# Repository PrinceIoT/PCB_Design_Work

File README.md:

Repository contain pcb design work done in both Kicard and Altium tools

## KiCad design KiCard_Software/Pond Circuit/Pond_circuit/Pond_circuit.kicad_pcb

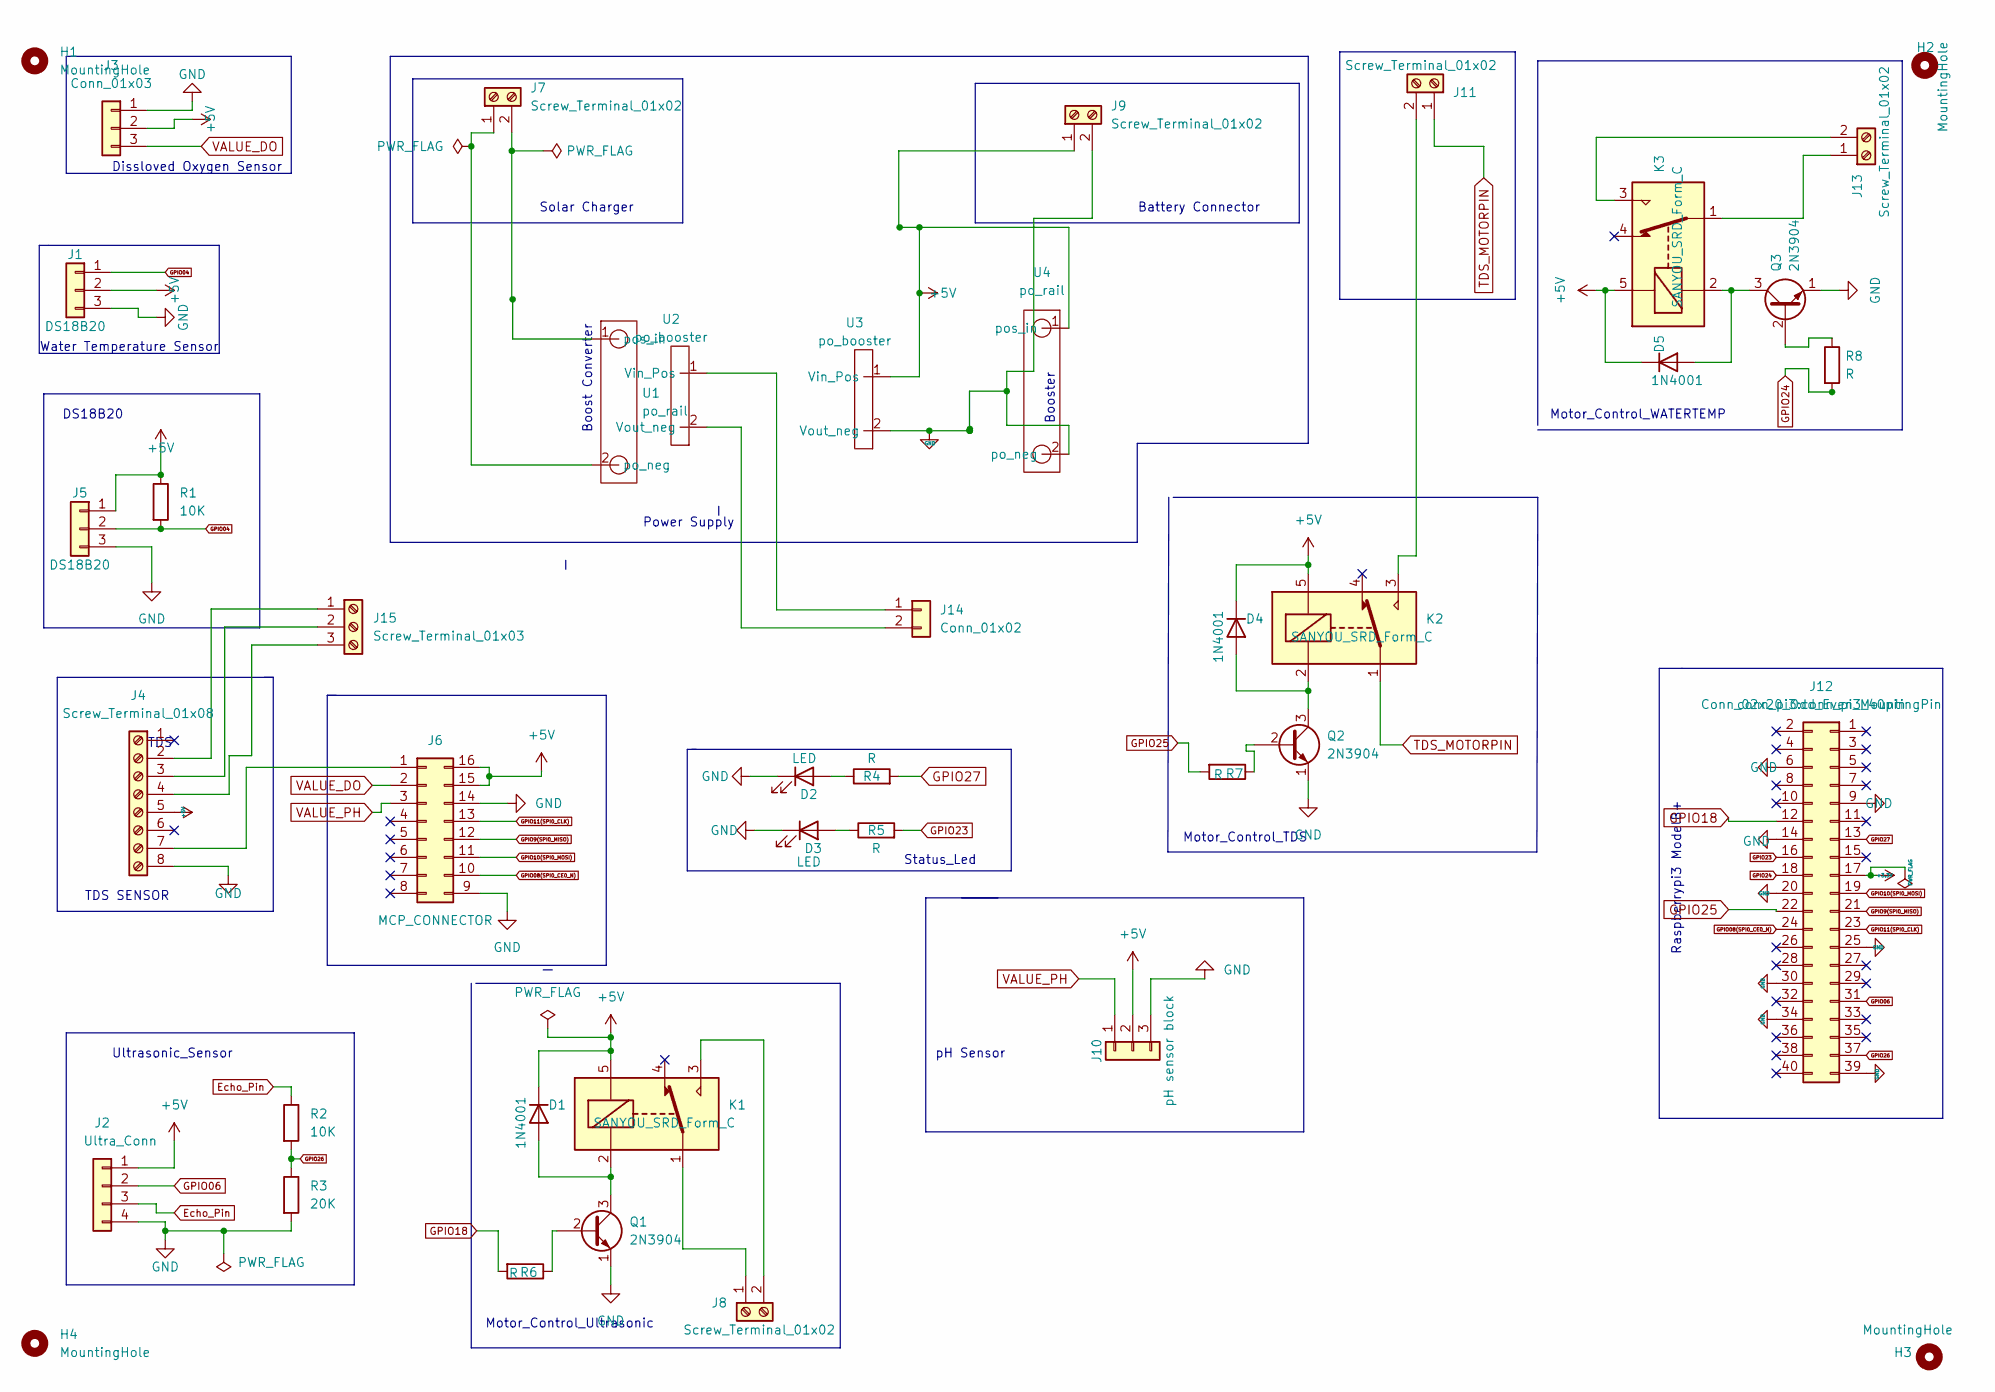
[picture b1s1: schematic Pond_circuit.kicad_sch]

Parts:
D1, D4, D5: 1N4001; D_DO-41_SOD81_P10.16mm_Horizontal
D2, D3: LED; LED_D3.0mm
H1, H2, H3, H4: MountingHole; MountingHole_2.5mm
J1: DS18B20; PinSocket_1x03_P1.00mm_Vertical
J2: Ultra_Conn; PinSocket_1x04_P1.00mm_Vertical
J3: Conn_01x03; PinSocket_1x03_P1.00mm_Vertical
J4: Screw_Terminal_01x08; TDS_FOOT
J5: DS18B20; con3_pin
J6: MCP_CONNECTOR; mcp3008_16
J7, J8, J9, J11, J13: Screw_Terminal_01x02; con2_pin
J10: pH sensor block; con3_pin
J12: Conn_02x20_Odd_Even_MountingPin; conn_pi3_40pin
J14: Conn_01x02; con2_pin
J15: Screw_Terminal_01x03; con3_pin
K1, K2, K3: SANYOU_SRD_Form_C; Relay_SPDT_SANYOU_SRD_Series_Form_C
Q1, Q2, Q3: 2N3904; TO-92_Inline
R1, R2: 10K; R_Axial_DIN0309_L9.0mm_D3.2mm_P12.70mm_Horizontal
R3: 20K; R_Axial_DIN0309_L9.0mm_D3.2mm_P12.70mm_Horizontal
R4, R5: R; R_Axial_DIN0309_L9.0mm_D3.2mm_P15.24mm_Horizontal
R6, R7, R8: R; R_Axial_DIN0411_L9.9mm_D3.6mm_P12.70mm_Horizontal
U1, U4: po_rail; buck_rail
U2, U3: po_booster; boost_rail

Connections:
+3V3: J12.17
+5V: D1.1 (K), D4.1 (K), D5.1 (K), J1.2, J2.1, J3.2, J4.5, J5.1, J6.15 (Pin_2b), J6.16 (Pin_1b), J9.1, J10.2, K1.5, K2.5, K3.5, R1.1, U3.1 (Vin_Pos), U4.1 (pos_in)
Echo_Pin: J2.3, R2.1
GND: D2.1 (K), D3.1 (K), J1.3, J2.4, J3.1, J4.8, J5.3, J6.9 (Pin_8b), J6.14 (Pin_3b), J9.2, J10.3, J12.6, J12.9, J12.14, J12.20, J12.25, J12.30, J12.34, J12.39, Q1.1 (E), Q2.1 (E), Q3.1 (E), R3.2, U3.2 (Vout_neg), U4.2 (po_neg)
GPIO04: J1.1, J5.2, R1.2
GPIO06: J2.2, J12.31
GPIO08(SPI0_CE0_N): J6.10 (Pin_7b), J12.24
GPIO9(SPI0_MISO): J6.12 (Pin_5b), J12.21
GPIO10(SPI0_MOSI): J6.11 (Pin_6b), J12.19
GPIO11(SPI0_CLK): J6.13 (Pin_4b), J12.23
GPIO18: J12.12, R6.2
GPIO23: J12.16, R5.2
GPIO24: J12.18, R8.2
GPIO25: J12.22, R7.2
GPIO26: J12.37, R2.2, R3.1
GPIO27: J12.13, R4.2
unnamed: D1.2 (A), K1.2, Q1.3 (C)
unnamed: D2.2 (A), R4.1
unnamed: D3.2 (A), R5.1
unnamed: D4.2 (A), K2.2, Q2.3 (C)
unnamed: D5.2 (A), K3.2, Q3.3 (C)
unnamed: J4.7, J6.1 (Pin_1a)
unnamed: J7.1, U1.2 (po_neg)
unnamed: J7.2, U1.1 (pos_in)
unnamed: J8.1, K1.1
unnamed: J8.2, K1.3
unnamed: J11.2, K2.3
unnamed: J13.1, K3.1
unnamed: J13.2, K3.3
unnamed: J14.1, U2.1 (Vin_Pos)
unnamed: J14.2, U2.2 (Vout_neg)
unnamed: J4.2, J15.1
unnamed: J4.3, J15.2
unnamed: J4.4, J15.3
unnamed: Q1.2 (B), R6.1
unnamed: Q2.2 (B), R7.1
unnamed: Q3.2 (B), R8.1
TDS_MOTORPIN: J11.1, K2.1
VALUE_DO: J3.3, J6.2 (Pin_2a)
VALUE_PH: J6.3 (Pin_3a), J10.1

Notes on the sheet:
Boost Converter
Dissloved Oxygen Sensor
TDS
Raspberrypi3 ModelB+
pH Sensor
TDS SENSOR
Status_Led
Water Temperature Sensor
Battery Connector
Power Supply
Motor_Control_TDS
Ultrasonic_Sensor
Motor_Control_Ultrasonic
Solar Charger
DS18B20
Booster
Motor_Control_WATERTEMP

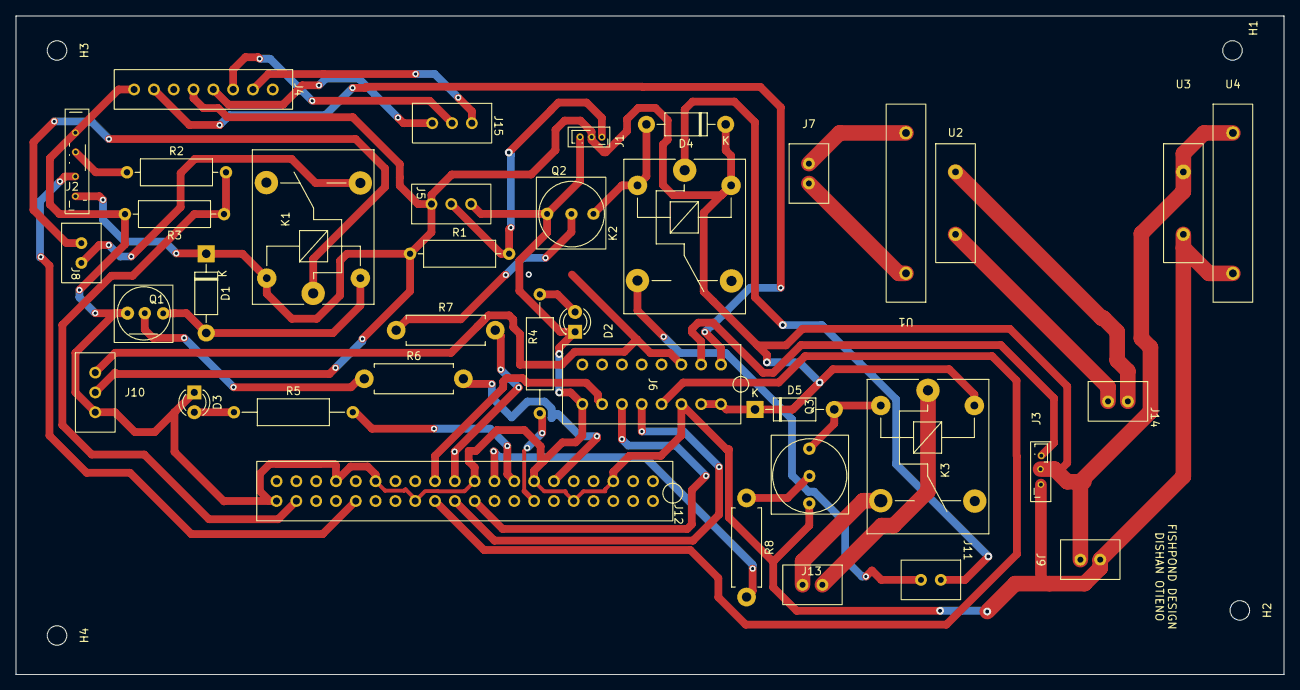
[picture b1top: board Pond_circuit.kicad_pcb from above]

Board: 2 copper layers, 162.6 x 84.4 mm, 42 parts (0 on the bottom side), 39 nets.

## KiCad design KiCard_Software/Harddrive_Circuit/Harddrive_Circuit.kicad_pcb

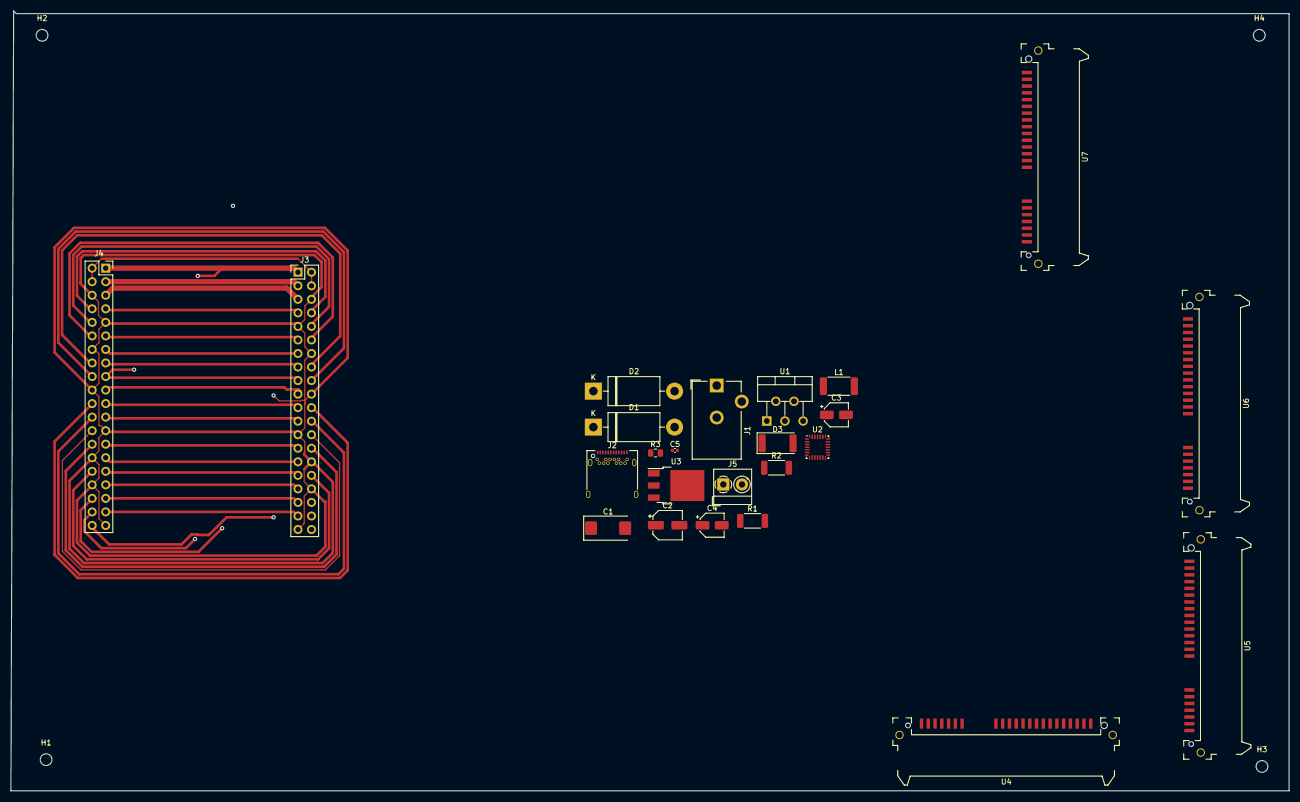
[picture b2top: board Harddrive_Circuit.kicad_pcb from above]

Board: 2 copper layers, 239.8 x 146.3 mm, 28 parts (0 on the bottom side), 42 nets.

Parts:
C1: 680uF; CP_EIA-7343-43_Kemet-X_Pad2.25x2.55mm_HandSolder
C2: 220uF; CP_Elec_5x5.8
C3: 10uF/50V; CP_Elec_4x3
C4: 22uF/50V; CP_Elec_4x4.5
C5: 0.1uF; C_0402_1005Metric
D1: 1N5400; D_DO-201AD_P15.24mm_Horizontal
D2: 1N5822; D_DO-201AD_P15.24mm_Horizontal
D3: LED; LED_2512_6332Metric
H1, H2, H3, H4: MountingHole; MountingHole_2.2mm_M2
J1: Barrel_Jack_Switch; BarrelJack_CUI_PJ-102AH_Horizontal
J2: USB_C_Receptacle; USB_C_Receptacle_Amphenol_12401548E4-2A
J3: Connector_Generic_Conn_02x20_Odd_Even; PinHeader_2x20_P2.54mm_Vertical
J4: Connector_Generic_Conn_02x20_Odd_Even; PinSocket_2x20_P2.54mm_Vertical
J5: Screw_Terminal_01x02; TerminalBlock_MetzConnect_Type059_RT06302HBWC_1x02_P3.50mm_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
L1: 33uH; L_2512_6332Metric
R1, R2: 5.1K; R_2010_5025Metric
R3: 220ohms; R_0805_2012Metric
U1: LM2596T-5; TO-220-5_P3.4x3.7mm_StaggerOdd_Lead3.8mm_Vertical
U2: MAX14661ETI_; QFN-28_4x4mm_P0.5mm
U3: LM1117-3.3; TO-252-3_TabPin2
U4, U5, U6, U7: sata; SATA_Amphenol_10029364-001LF_Horizontal

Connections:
5V: J3.2, J3.4, J4.2, J4.4
+3.3V: J3.1, J3.17, J4.1, J4.17
+3V3: C4.1, C5.1, U2.1 (SPI/~I2C), U2.22 (~SD), U2.26 (VCC), U3.2 (VO)
+5V: C2.1, C3.1, J2.A4 (VBUS), J2.A9 (VBUS), J2.B4 (VBUS), J2.B9 (VBUS), J5.2, L1.2, R3.1, U1.4 (FB), U3.3 (VI)
+12V: D1.1 (K), U1.1 (VIN)
GND: C1.2, C2.2, C3.2, C4.2, C5.2, D2.2 (A), D3.1 (K), J1.2, J1.3, J2.A1 (GND), J2.A12 (GND), J2.B1 (GND), J2.B12 (GND), J2.S1 (SHIELD), J3.6, J3.9, J3.14, J3.20, J3.25, J3.30, J3.34, J3.39, J4.6, J4.9, J4.14, J4.20, J4.25, J4.30, J4.34, J4.39, J5.1, R1.2, R2.2, U1.3 (GND), U2.11 (GND), U2.25 (GND), U3.1 (GND)
GPIO2_SDA1: J4.3, U2.27 (DIN/SDA)
GPIO3_SCL1: J3.5, J4.5
GPIO4_GPIO_GCLK: J3.7, J4.7
GPIO5: J3.29, J4.29
GPIO6: J3.31, J4.31
GPIO7_SPI_CE1_N: J3.26, J4.26
GPIO8_SPI_CE0_N: J4.24, U2.23 (CS/A0)
GPIO9_SPI_MISO: J3.21, J4.21
GPIO10_SPI_MOSI: J3.19, J4.19
GPIO11_SPI_SCLK: J4.23, U2.24 (SCLK/SCL)
GPIO12: J3.32, J4.32
GPIO13: J3.33, J4.33
GPIO14_TXD0: J3.8, J4.8
GPIO15_RXD0: J3.10, J4.10
GPIO16: J3.36, J4.36
GPIO17_GEN0: J3.11, J4.11
GPIO18_GEN1: J3.12, J4.12
GPIO19: J3.35, J4.35
GPIO20: J3.38, J4.38
GPIO21: J3.40, J4.40
GPIO22_GEN3: J3.15, J4.15
GPIO23_GEN4: J3.16, J4.16
GPIO24_GEN5: J3.18, J4.18
GPIO25_GEN6: J3.22, J4.22
GPIO26: J3.37, J4.37
GPIO27_GEN2: J3.13, J4.13
ID_SC: J3.28, J4.28
ID_SD: J3.27, J4.27
unnamed: C1.1, U1.5 (~ON/OFF)
unnamed: D1.2 (A), J1.1
unnamed: D2.1 (K), L1.1, U1.2 (OUT)
unnamed: D3.2 (A), R3.2
unnamed: J2.A5 (CC1), R1.1
unnamed: J2.A6 (D+), J2.B6 (D+), U2.13 (COMB)
unnamed: J2.A7 (D-), J2.B7 (D-), U2.10 (COMA)
unnamed: J2.B5 (CC2), R2.1

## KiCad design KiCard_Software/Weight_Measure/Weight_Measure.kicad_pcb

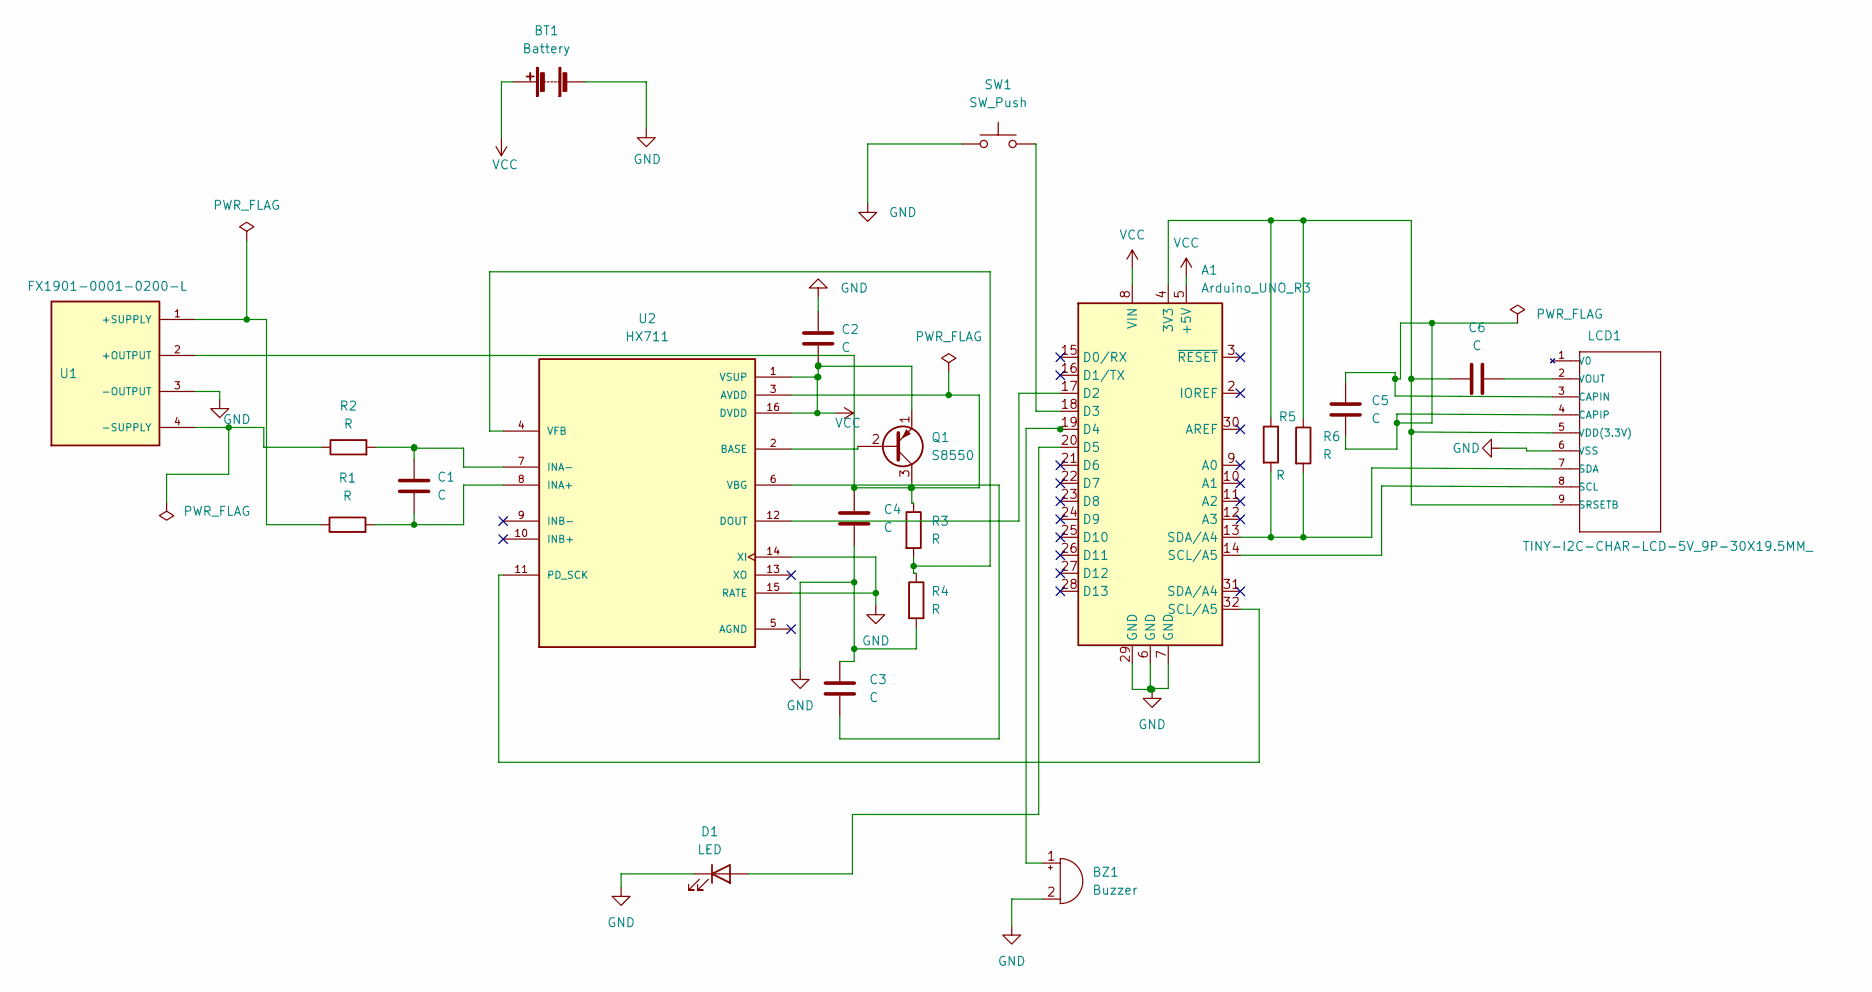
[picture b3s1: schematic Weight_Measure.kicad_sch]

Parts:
A1: Arduino_UNO_R3; Arduino_UNO_R3_WithMountingHoles
BT1: Battery; BatteryHolder_Bulgin_BX0036_1xC
BZ1: Buzzer; Buzzer_D14mm_H7mm_P10mm
C1, C2, C3, C4, C5, C6: C; C_Axial_L3.8mm_D2.6mm_P12.50mm_Horizontal
D1: LED; LED_D3.0mm
LCD1: TINY-I2C-CHAR-LCD-5V_9P-30X19.5MM_; LCD9-1.5-30X19.5MM; MPN 12 LCD Breadout
Q1: S8550; TO-92_Inline
R1, R2, R3, R4, R5, R6: R; R_Axial_DIN0309_L9.0mm_D3.2mm_P15.24mm_Horizontal
SW1: SW_Push; SW_PUSH_6mm
U1: FX1901-0001-0200-L; SENSOR_FX1901-0001-0200-L
U2: HX711; SOP127P600X180-16N; PARTREV V2.0

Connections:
GND: A1.6 (GND), A1.7 (GND), A1.29 (GND), BT1.2 (-), BZ1.2 (+), C2.1, C3.1, C4.2, D1.1 (K), LCD1.6 (VSS), R4.2, SW1.1, U1.3 (-OUTPUT), U2.14 (XI), U2.15 (RATE)
unnamed: A1.4 (3V3), C6.1, LCD1.5 (VDD(3.3V)), LCD1.9 (SRSETB), R5.1, R6.1
unnamed: A1.13 (SDA/A4), LCD1.7 (SDA), R5.2, R6.2
unnamed: A1.14 (SCL/A5), LCD1.8 (SCL)
unnamed: A1.17 (D2), U2.12 (DOUT)
unnamed: A1.18 (D3), SW1.2
unnamed: A1.19 (D4), BZ1.1 (-)
unnamed: A1.20 (D5), D1.2 (A)
unnamed: A1.32 (SCL/A5), U2.11 (PD_SCK)
unnamed: C1.1, R2.2, U2.7 (INA-)
unnamed: C1.2, R1.2, U2.8 (INA+)
unnamed: C3.2, U2.6 (VBG)
unnamed: C4.1, U1.2 (+OUTPUT)
unnamed: C5.1, C5.2, LCD1.3 (CAPIN), LCD1.4 (CAPIP)
unnamed: C6.2, LCD1.2 (VOUT)
unnamed: Q1.2 (B), U2.2 (BASE)
unnamed: Q1.3 (C), R3.1, U2.3 (AVDD)
unnamed: R1.1, U1.1 (+SUPPLY)
unnamed: R2.1, U1.4 (-SUPPLY)
unnamed: R3.2, R4.1, U2.4 (VFB)
VCC: A1.5 (+5V), A1.8 (VIN), BT1.1 (+), C2.2, Q1.1 (E), U2.1 (VSUP), U2.16 (DVDD)

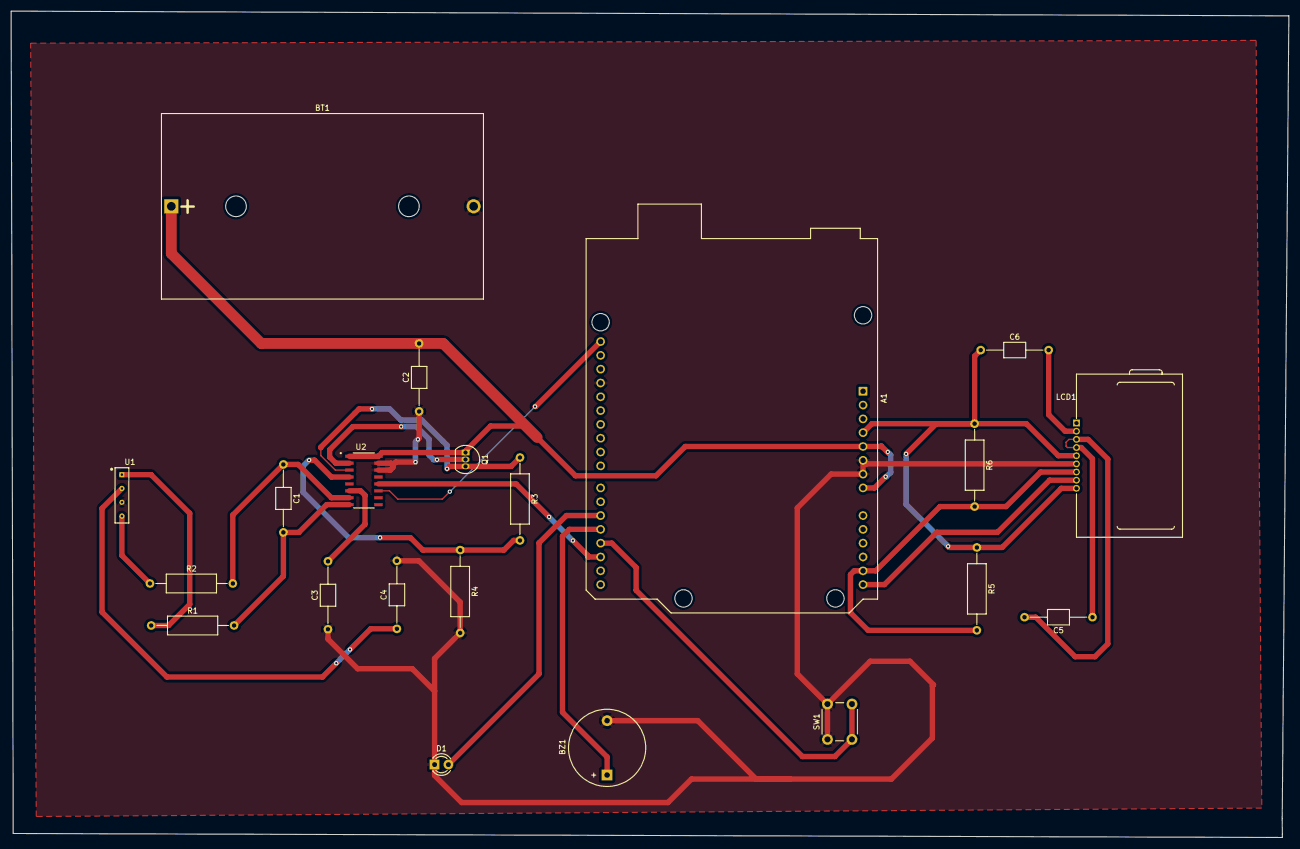
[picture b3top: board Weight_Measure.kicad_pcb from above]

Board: 2 copper layers, 235.0 x 152.0 mm, 21 parts (0 on the bottom side), 21 nets.

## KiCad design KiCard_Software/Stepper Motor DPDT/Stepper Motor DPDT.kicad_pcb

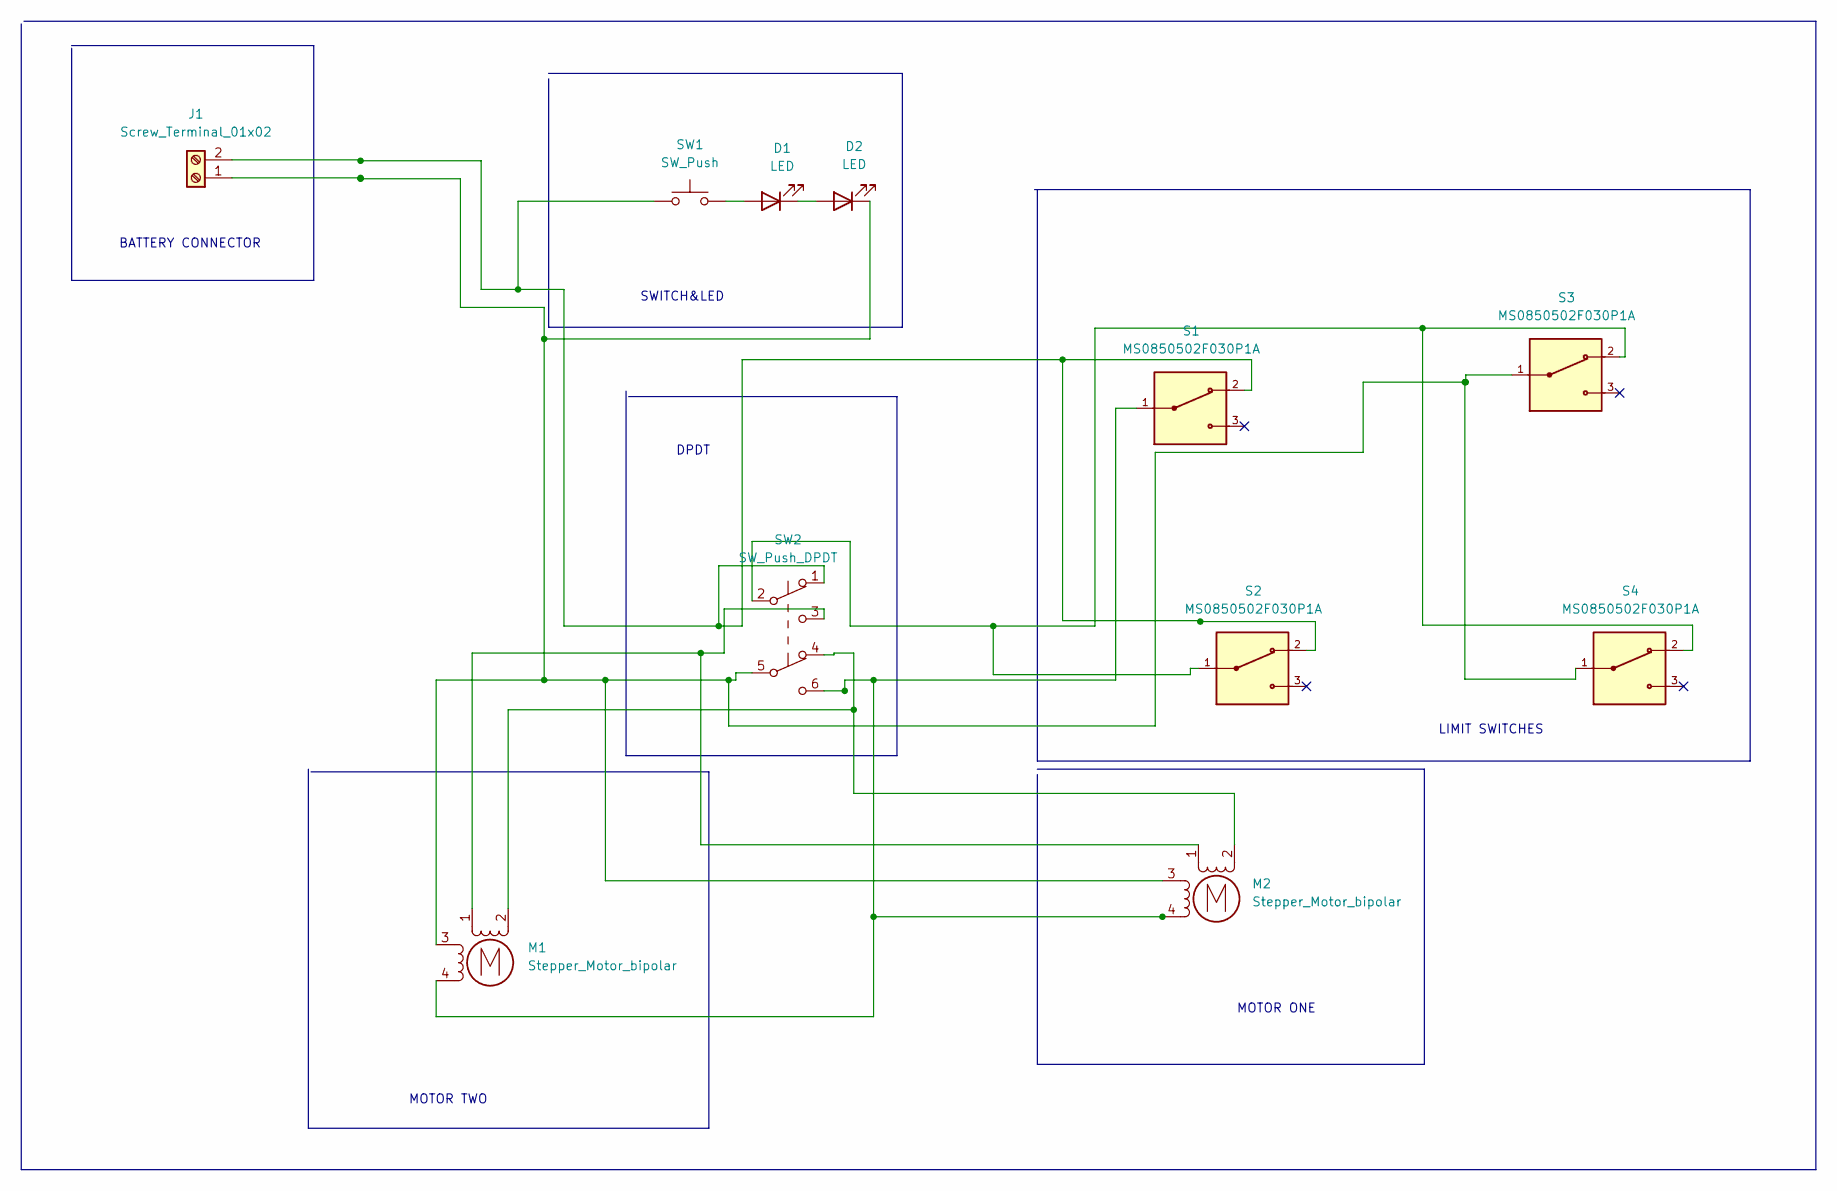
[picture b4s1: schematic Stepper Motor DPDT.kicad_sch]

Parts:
D1, D2: LED; LED_D3.0mm_Clear
J1: Screw_Terminal_01x02; TerminalBlock_Phoenix_MKDS-3-2-5.08_1x02_P5.08mm_Horizontal
M1, M2: Stepper_Motor_bipolar; TerminalBlock_MetzConnect_Type059_RT06304HBWC_1x04_P3.50mm_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
S1, S2, S3, S4: MS0850502F030P1A; SW_MS0850502F030P1A
SW1: SW_Push; SW_PUSH_6mm
SW2: SW_Push_DPDT; SW_E-Switch_EG2219_DPDT_Angled

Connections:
unnamed: D1.1 (K), D2.2 (A)
unnamed: D1.2 (A), SW1.2
unnamed: D2.1 (K), J1.1, M1.3, M2.3, S3.1, S4.1, SW2.5 (B)
unnamed: J1.2, S1.2, S2.2, SW1.1, SW2.1 (A)
unnamed: M1.1, M2.1, SW2.3 (C)
unnamed: M1.2 (-), M2.2 (-), SW2.4 (A)
unnamed: M1.4, M2.4, S1.1, SW2.6 (C)
unnamed: S2.1, S3.2, S4.2, SW2.2 (B)

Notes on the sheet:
DPDT
SWITCH&LED
MOTOR TWO
MOTOR ONE
LIMIT SWITCHES
BATTERY CONNECTOR

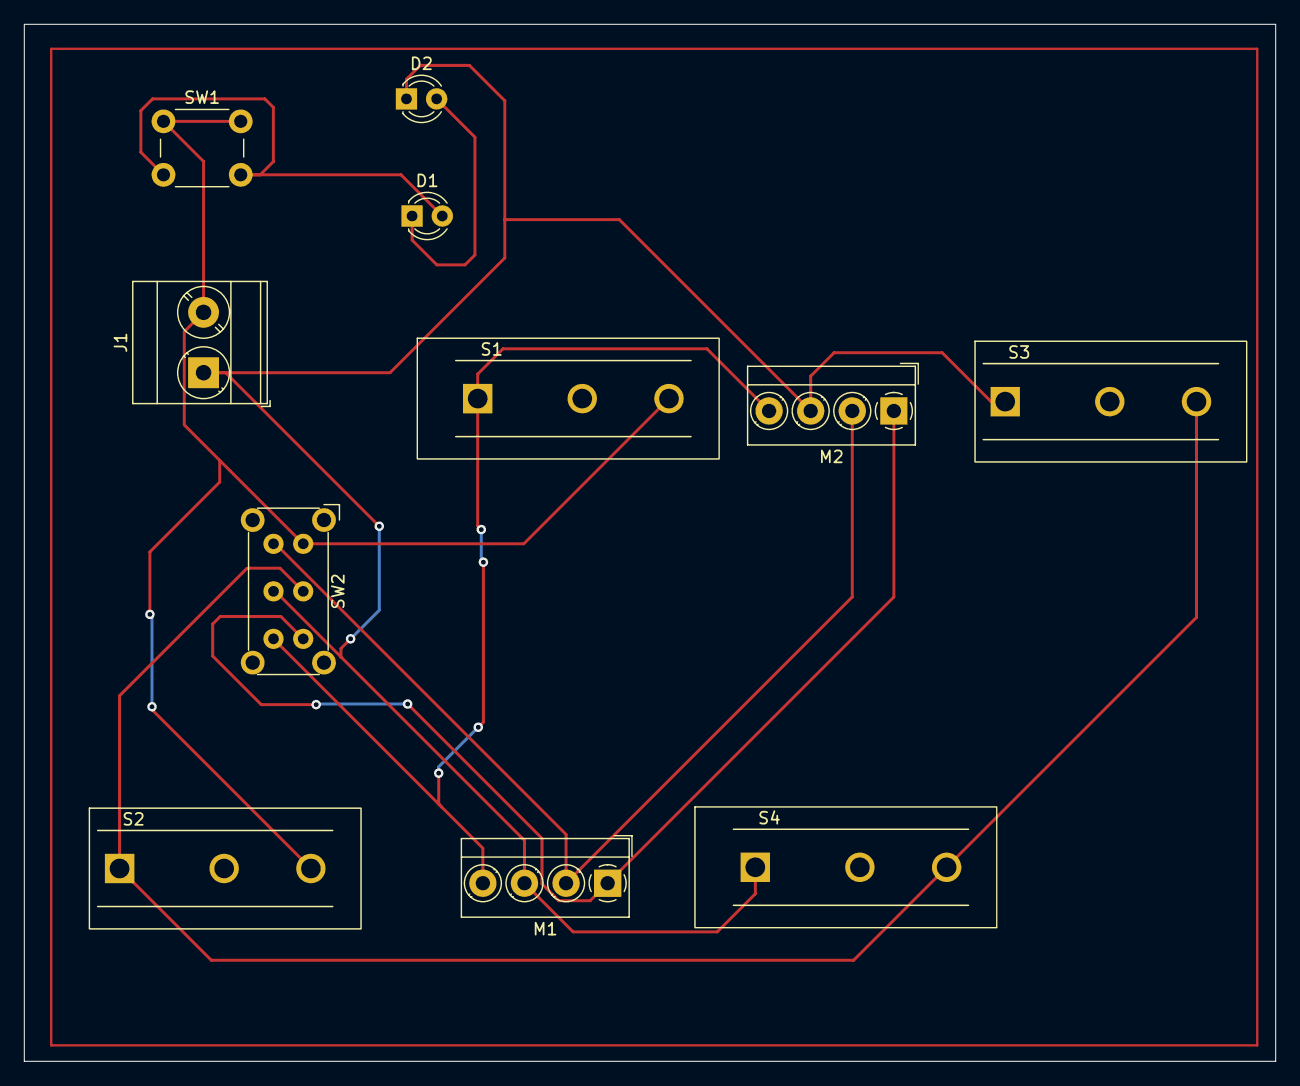
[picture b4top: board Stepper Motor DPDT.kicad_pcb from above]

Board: 2 copper layers, 105.3 x 87.3 mm, 11 parts (0 on the bottom side), 8 nets.

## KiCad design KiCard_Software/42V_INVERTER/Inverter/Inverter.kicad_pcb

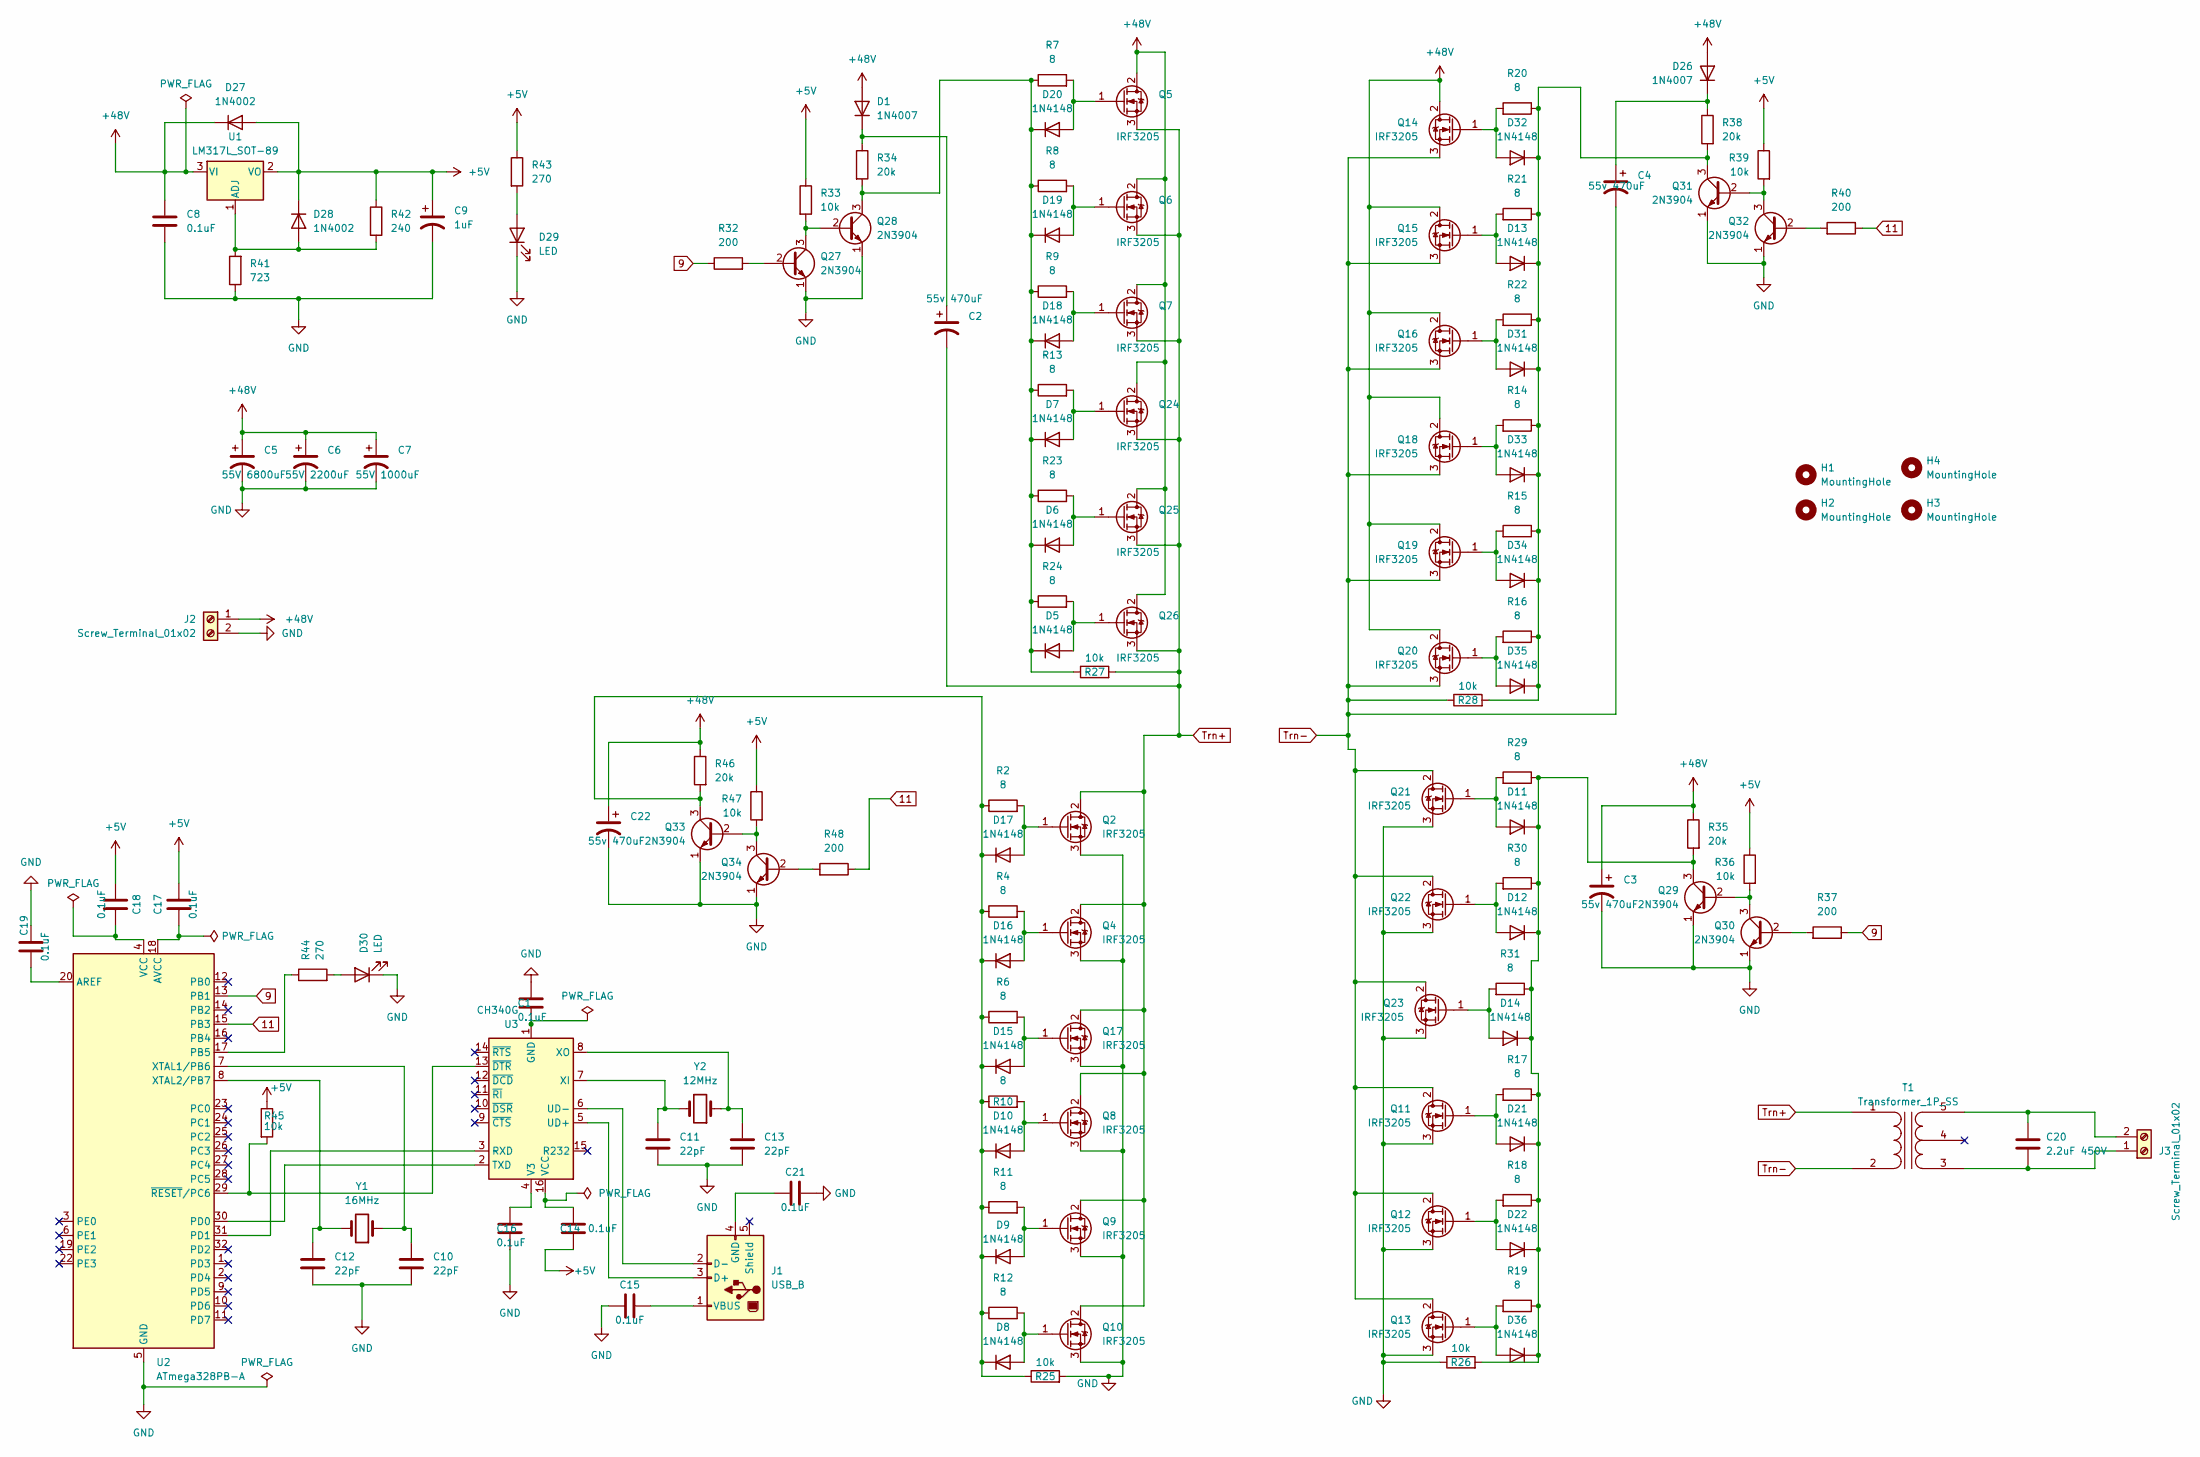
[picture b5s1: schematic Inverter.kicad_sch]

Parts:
C1, C8, C14, C15, C16, C17, C18, C19, C21: 0.1uF; C_Radial_D6.3mm_H7.0mm_P2.50mm
C2, C3, C4, C22: 55v 470uF; CP_Radial_D6.3mm_P2.50mm
C5: 55V 6800uF; CP_Elec_6.3x5.9
C6: 55V 2200uF; CP_Elec_6.3x5.9
C7: 55V 1000uF; CP_Elec_6.3x5.7
C9: 1uF; CP_Radial_D6.3mm_P2.50mm
C10, C11, C12, C13: 22pF; C_Disc_D3.8mm_W2.6mm_P2.50mm
C20: 2.2uF 450V; C_Rect_L18.0mm_W5.0mm_P15.00mm_FKS3_FKP3
D1, D26: 1N4007; D_DO-41_SOD81_P10.16mm_Horizontal
D5, D6, D7, D8, D9, D10, D11, D12, D13, D14, D15, D16, D17, D18, D19, D20, D21, D22, D31, D32, D33, D34, D35, D36: 1N4148; D_DO-35_SOD27_P7.62mm_Horizontal
D27, D28: 1N4002; D_DO-41_SOD81_P10.16mm_Horizontal
D29: LED; LED_1206_3216Metric
D30: LED; LED_2010_5025Metric
H1, H2, H3, H4: MountingHole; MountingHole_2.2mm_M2
J1: USB_B; USB_A_CNCTech_1001-011-01101_Horizontal
J2, J3: Screw_Terminal_01x02; TerminalBlock_Phoenix_MKDS-3-2-5.08_1x02_P5.08mm_Horizontal
Q2, Q4, Q5, Q6, Q7, Q8, Q9, Q10, Q11, Q12, Q13, Q14, Q15, Q16, Q17, Q18, Q19, Q20, Q21, Q22, Q23, Q24, Q25, Q26: IRF3205; TO-220-3_Vertical
Q27, Q28, Q29, Q30, Q31, Q32, Q33, Q34: 2N3904; TO-92_Inline_Wide
R2, R4, R6, R7, R8, R9, R10, R11, R12, R13, R14, R15, R16, R17, R18, R19, R20, R21, R22, R23, R24, R29, R30, R31: 8; R_Axial_DIN0309_L9.0mm_D3.2mm_P15.24mm_Horizontal
R25, R26, R27, R28, R33, R36, R39, R45, R47: 10k; R_Axial_DIN0309_L9.0mm_D3.2mm_P15.24mm_Horizontal
R32, R37, R40, R48: 200; R_Axial_DIN0207_L6.3mm_D2.5mm_P10.16mm_Horizontal
R34, R35, R38, R46: 20k; R_Axial_DIN0309_L9.0mm_D3.2mm_P15.24mm_Horizontal
R41: 723; R_Axial_DIN0207_L6.3mm_D2.5mm_P10.16mm_Horizontal
R42: 240; R_Axial_DIN0207_L6.3mm_D2.5mm_P10.16mm_Horizontal
R43, R44: 270; R_Axial_DIN0207_L6.3mm_D2.5mm_P10.16mm_Horizontal
T1: Transformer_1P_SS; Transformer_MACOM_SM-22
U1: LM317L_SOT-89; SOT-89-3
U2: ATmega328PB-A; TQFP-32_7x7mm_P0.8mm
U3: CH340G; SOIC-16_3.9x9.9mm_P1.27mm
Y1: 16MHz; Crystal_SMD_HC49-SD
Y2: 12MHz; Crystal_SMD_HC49-SD

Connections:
9: R32.1, R37.1, U2.13 (PB1)
11: R40.1, R48.1, U2.15 (PB3); also elsewhere on the board
unnamed: C2.1, D1.1 (K), R34.1
unnamed: D5.2 (A), Q26.1 (G), R24.2
unnamed: D6.2 (A), Q25.1 (G), R23.2
unnamed: D7.2 (A), Q24.1 (G), R13.2
unnamed: D8.2 (A), Q10.1 (G), R12.2
unnamed: D9.2 (A), Q9.1 (G), R11.2
unnamed: D10.2 (A), Q8.1 (G), R10.2
unnamed 9: D8.1 (K), D9.1 (K), D10.1 (K), D15.1 (K), D16.1 (K), D17.1 (K), Q33.3 (C), R2.1, R4.1, R6.1, R10.1, R11.1, R12.1, R25.1, R46.2; also elsewhere on the board
unnamed: D11.2 (A), Q21.1 (G), R29.2
unnamed: D11.1 (K), D12.1 (K), D14.1 (K), D21.1 (K), D22.1 (K), D36.1 (K), Q29.3 (C), R17.1, R18.1, R19.1, R26.2, R29.1, R30.1, R31.1, R35.2
unnamed: D12.2 (A), Q22.1 (G), R30.2
unnamed: D13.2 (A), Q15.1 (G), R21.2
unnamed: D13.1 (K), D31.1 (K), D32.1 (K), D33.1 (K), D34.1 (K), D35.1 (K), Q31.3 (C), R14.1, R15.1, R16.1, R20.1, R21.1, R22.1, R28.2, R38.2
unnamed: D14.2 (A), Q23.1 (G), R31.2
unnamed: D15.2 (A), Q17.1 (G), R6.2
unnamed: D16.2 (A), Q4.1 (G), R4.2
unnamed: D17.2 (A), Q2.1 (G), R2.2
unnamed: D18.2 (A), Q7.1 (G), R9.2
unnamed: D5.1 (K), D6.1 (K), D7.1 (K), D18.1 (K), D19.1 (K), D20.1 (K), Q28.3 (C), R7.1, R8.1, R9.1, R13.1, R23.1, R24.1, R27.1, R34.2
unnamed: D19.2 (A), Q6.1 (G), R8.2
unnamed: D20.2 (A), Q5.1 (G), R7.2
unnamed: D21.2 (A), Q11.1 (G), R17.2
unnamed: D22.2 (A), Q12.1 (G), R18.2
unnamed: C4.1, D26.1 (K), R38.1
unnamed: D28.2 (A), R41.2, R42.2, U1.1 (ADJ)
unnamed: D29.2 (A), R43.2
unnamed: D30.2 (A), R44.2
unnamed: D31.2 (A), Q16.1 (G), R22.2
unnamed: D32.2 (A), Q14.1 (G), R20.2
unnamed: D33.2 (A), Q18.1 (G), R14.2
unnamed: D34.2 (A), Q19.1 (G), R15.2
unnamed: D35.2 (A), Q20.1 (G), R16.2
unnamed: D36.2 (A), Q13.1 (G), R19.2
unnamed: J1.3 (D+), U3.5 (UD+)
unnamed: J1.2 (D-), U3.6 (UD-)
unnamed: C21.1, J1.4 (GND)
unnamed: C15.2, J1.1 (VBUS)
unnamed: C20.2, J3.1, T1.3 (SA)
unnamed: C20.1, J3.2, T1.5 (SB)
unnamed: Q27.2 (B), R32.2
unnamed: Q27.3 (C), Q28.2 (B), R33.2
unnamed: Q29.2 (B), Q30.3 (C), R36.2
unnamed: Q30.2 (B), R37.2
unnamed: Q31.2 (B), Q32.3 (C), R39.2
unnamed: Q32.2 (B), R40.2
unnamed: Q33.2 (B), Q34.3 (C), R47.2
unnamed: Q34.2 (B), R48.2
unnamed: C19.1, U2.20 (AREF)
unnamed: C17.1, U2.18 (AVCC)
unnamed: R44.1, U2.17 (PB5)
unnamed: U2.30 (PD0), U3.2 (TXD)
unnamed: U2.31 (PD1), U3.3 (RXD)
unnamed: C18.2, U2.4 (VCC)
unnamed: C10.1, U2.7 (XTAL1/PB6), Y1.1
unnamed: C12.1, U2.8 (XTAL2/PB7), Y1.2
unnamed: R45.2, U2.29 (~RESET/PC6), U3.13 (~DTR)
unnamed: C16.2, U3.4 (V3)
unnamed: C14.2, U3.16 (VCC)
unnamed: C11.1, U3.7 (XI), Y2.2
unnamed: C13.1, U3.8 (XO), Y2.1
Trn+: C2.2, Q2.2 (D), Q4.2 (D), Q5.3 (S), Q6.3 (S), Q7.3 (S), Q8.2 (D), Q9.2 (D), Q10.2 (D), Q17.2 (D), Q24.3 (S), Q25.3 (S), Q26.3 (S), R27.2, T1.1 (AA)
Trn-: C4.2, Q11.2 (D), Q12.2 (D), Q13.2 (D), Q14.3 (S), Q15.3 (S), Q16.3 (S), Q18.3 (S), Q19.3 (S), Q20.3 (S), Q21.2 (D), Q22.2 (D), Q23.2 (D), R28.1, T1.2 (AB)

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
